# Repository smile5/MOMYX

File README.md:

# OMYXAir
OMYXAir is an extremely simple but sophiticated Respiratory system:
An Open Source, Low Tech, Low Cost Ventilator

Picture of the complete system :

The System can be monitor by a PC (Linux-Windows-MAC) or Rpi or any other Linux Board, the interface is shown below:

# LICENSE :

This project is under [CERN-OHL-S v2 or ater] (https://ohwr.org/cern_ohl_s_v2.txt) for Hardware, [GPL-v3] (http://www.gnu.org/licenses/gpl-3.0.txt) for Software, and [Creative Commons Zero] (https://creativecommons.org/publicdomain/zero/1.0/legalcode.fr) for Documentation

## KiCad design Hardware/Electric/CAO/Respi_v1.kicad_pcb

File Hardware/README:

Hardware source:
Valve design
Venturi design
Electrical schematic

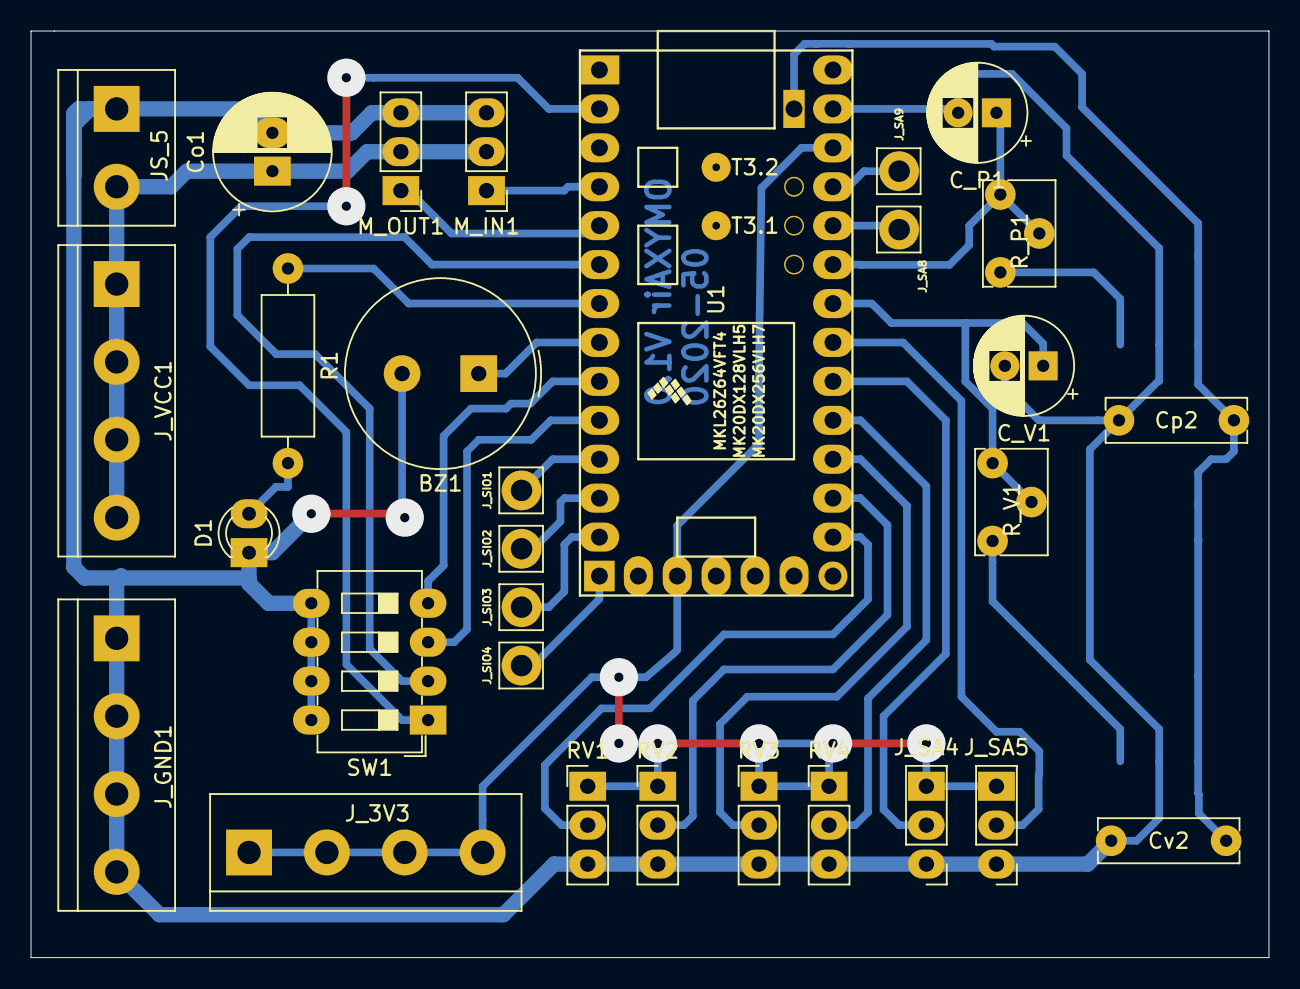
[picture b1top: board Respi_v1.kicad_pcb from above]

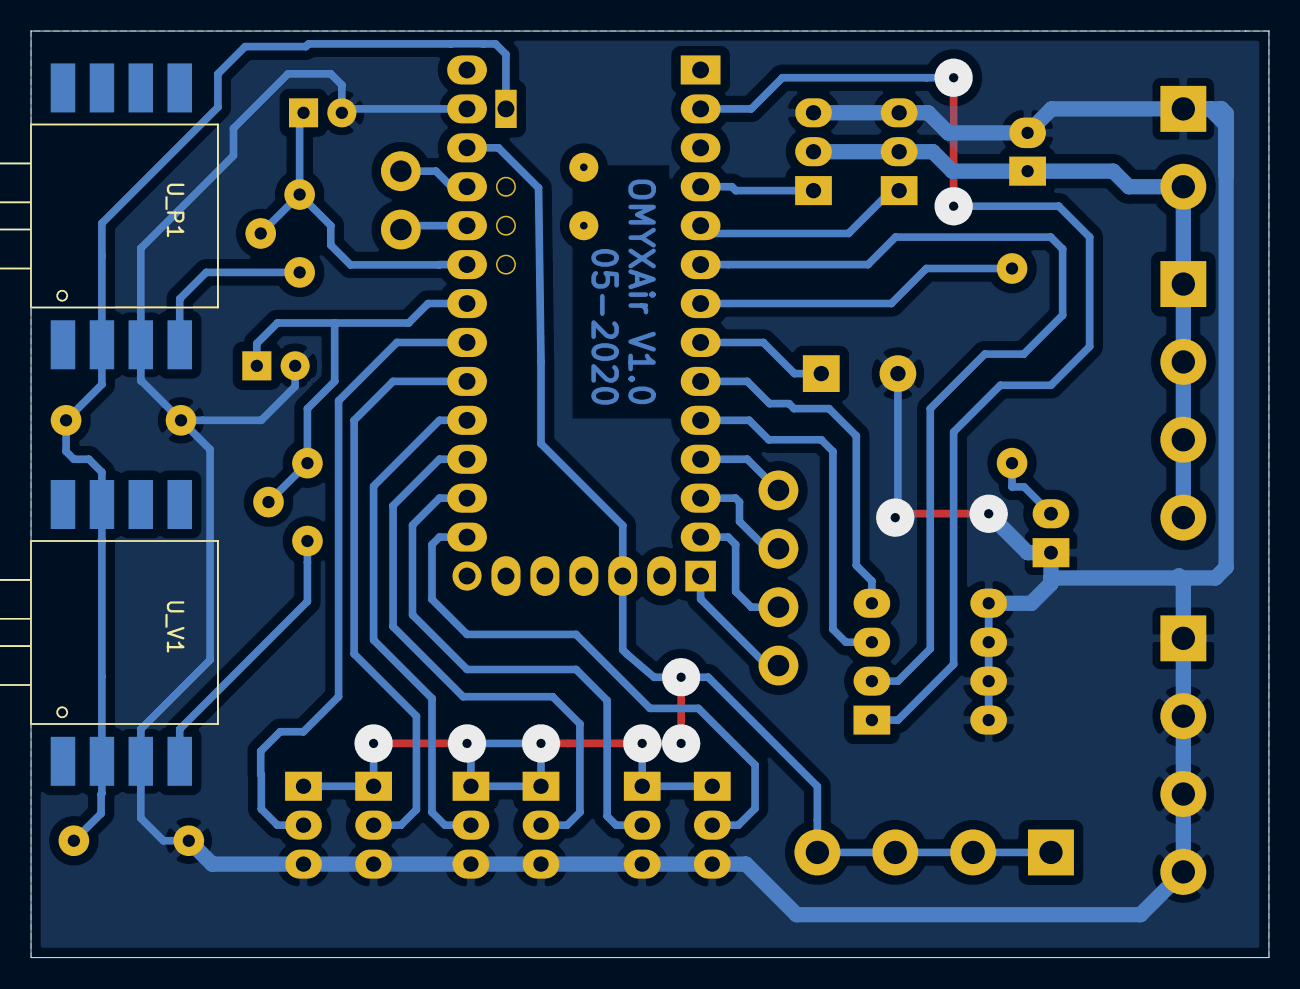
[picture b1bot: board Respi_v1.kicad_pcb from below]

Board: 2 copper layers, 80.8 x 60.5 mm, 32 parts (2 on the bottom side), 29 nets.

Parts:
BZ1: Buzzer; Buzzer_TDK_PS1240P02BT_D12.2mm_H6.5mm
C_P1: 100uF; CP_Radial_D6.3mm_P2.50mm
C_V1: 10uF; CP_Radial_D6.3mm_P2.50mm
Co1: 470uF; CP_Radial_D7.5mm_P2.50mm
Cp2: 10nF; C_Rect_L9.0mm_W2.7mm_P7.50mm_MKT
Cv2: 10nF; C_Rect_L9.0mm_W2.7mm_P7.50mm_MKT
D1: LED; LED_D3.0mm
JS_5: Conn_01x02; TerminalBlock_bornier-2_P5.08mm
J_3V3: Conn_01x04; TerminalBlock_bornier-4_P5.08mm
J_GND1: Conn_01x04; TerminalBlock_bornier-4_P5.08mm
J_SA4, J_SA5: Conn_01x03; PinHeader_1x03_P2.54mm_Vertical
J_SA8, J_SA9: Conn_01x01; Pin_D1.4mm_L8.5mm_W2.8mm_FlatFork
J_SIO1, J_SIO2, J_SIO3, J_SIO4: Conn_01x01; Pin_D1.4mm_L8.5mm_W2.8mm_FlatFork
J_VCC1: Conn_01x04; TerminalBlock_bornier-4_P5.08mm
M_IN1: Motor_Servo_Futaba_J; PinHeader_1x03_P2.54mm_Vertical
M_OUT1: Motor_Servo_Futaba_J; PinHeader_1x03_P2.54mm_Vertical
R1: 330; R_Axial_DIN0309_L9.0mm_D3.2mm_P12.70mm_Horizontal
RV1, RV2, RV3, RV4: 10k; PinHeader_1x03_P2.54mm_Vertical
R_P1: 1k; Potentiometer_Bourns_3266W_Vertical
R_V1: 1,7k; Potentiometer_Bourns_3266W_Vertical
SW1: SW_DIP_x04; SW_DIP_SPSTx04_Slide_6.7x11.72mm_W7.62mm_P2.54mm_LowProfile
U1: Teensy3.2; Teensy30_31_32_LC
U_P1: MPXV50xxDP; MPXV_SOP
U_V1: MPXV50xxDP; MPXV_SOP

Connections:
+3V3: J_3V3.1, J_3V3.2, J_3V3.3, J_3V3.4, J_SA4.3, J_SA5.3, RV1.1, RV2.1, RV3.1, RV4.1, U1.16, U1.31
+5V: Cp2.1, Cv2.1, U1.34, U_P1.2, U_V1.2, U_V1.7
/A0_Cy: RV1.2, U1.21
/A1_IE: RV2.2, U1.22
/A2_Pinsp: RV3.2, U1.23
/A3_PExp: RV4.2, U1.24
/A6_Venturi: C_V1.1, R_V1.1, R_V1.2, U1.27
/A7_Pression: C_P1.1, R_P1.1, R_P1.2, U1.28
/Calib_8: SW1.3, U1.10
/IO1: SW1.1, U1.2
/IO6: SW1.2, U1.6
/Maint_7: SW1.4, U1.9
/SA4: J_SA4.2, U1.25
/SA5: J_SA5.2, U1.26
/SA8: J_SA8.1, U1.29
/SA9: J_SA9.1, U1.30
/SIO1: J_SIO1.1, U1.11
/SIO2: J_SIO2.1, U1.12
/SIO3: J_SIO3.1, U1.13
/SIO4: J_SIO4.1, U1.14
/Servo_Valve_In: M_IN1.1, U1.4
/Servo_Valve_Out: M_OUT1.1, U1.5
GNDPWR: BZ1.2, C_P1.2, C_V1.2, Co1.2, Cp2.2, Cv2.2, D1.1, JS_5.1, J_GND1.1, J_GND1.2, J_GND1.3, J_GND1.4, J_SA4.1, J_SA5.1, M_IN1.3, M_OUT1.3, RV1.3, RV2.3, RV3.3, RV4.3, SW1.5, SW1.6, SW1.7, SW1.8, U1.32, U_P1.3, U_V1.3
unnamed: BZ1.1, U1.8
unnamed: D1.2, R1.2
unnamed: R1.1, U1.7
unnamed: R_P1.3, U_P1.4
unnamed: R_V1.3, U_V1.4
VCC: Co1.1, JS_5.2, J_VCC1.1, J_VCC1.2, J_VCC1.3, J_VCC1.4, M_IN1.2, M_OUT1.2

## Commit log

2020-05-03 Create Hardware
2020-05-15 Rename MOMYX_V1.ino to OMYXAir_V1_alpha.ino
2020-05-20 Rename file
2020-05-20 Add Firmware GUI
2020-05-20 Add GUI
2020-05-20 Add CAO Elec
2020-06-02 Create Turbines
2020-06-02 Update Turbines
2020-06-11 Create Valve VTT V2
2020-06-30 Create Valve double V8
2020-06-30 Create Sonde Pito
2020-06-30 Create Pito DZ V3
